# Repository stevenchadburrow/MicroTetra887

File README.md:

# MicroTetra887
<b>Two-player "Tetra" through 16-color VGA on a PIC16F887</b><br>

The goal of this project was a challenge to do more with less.  I have used the PIC24 and PIC32 various times to generate VGA signals and play video games, but the PIC16 has far less capability.  "Tetra" is very easy to implement and one of my favorite games, so it was the target for this device.  Space allowed for there to be two players simultaneously.

Specifications:<br>
- Only IC is the PIC16F887<br>
- Runs at 5 MIPS (20 MHz clock)<br>
- 368 bytes of RAM<br>
- VGA resolution of 24x22 pixels at 16 colors<br>
- Two-player "Tetra" through homebrew or Genesis controllers<br>
- PCB's double as both the console and controllers<br>

<table>
  <tr><td></td><td></td></tr>
  <tr><td></td><td></td></tr>
  <tr><td></td><td></td></tr>
</table>

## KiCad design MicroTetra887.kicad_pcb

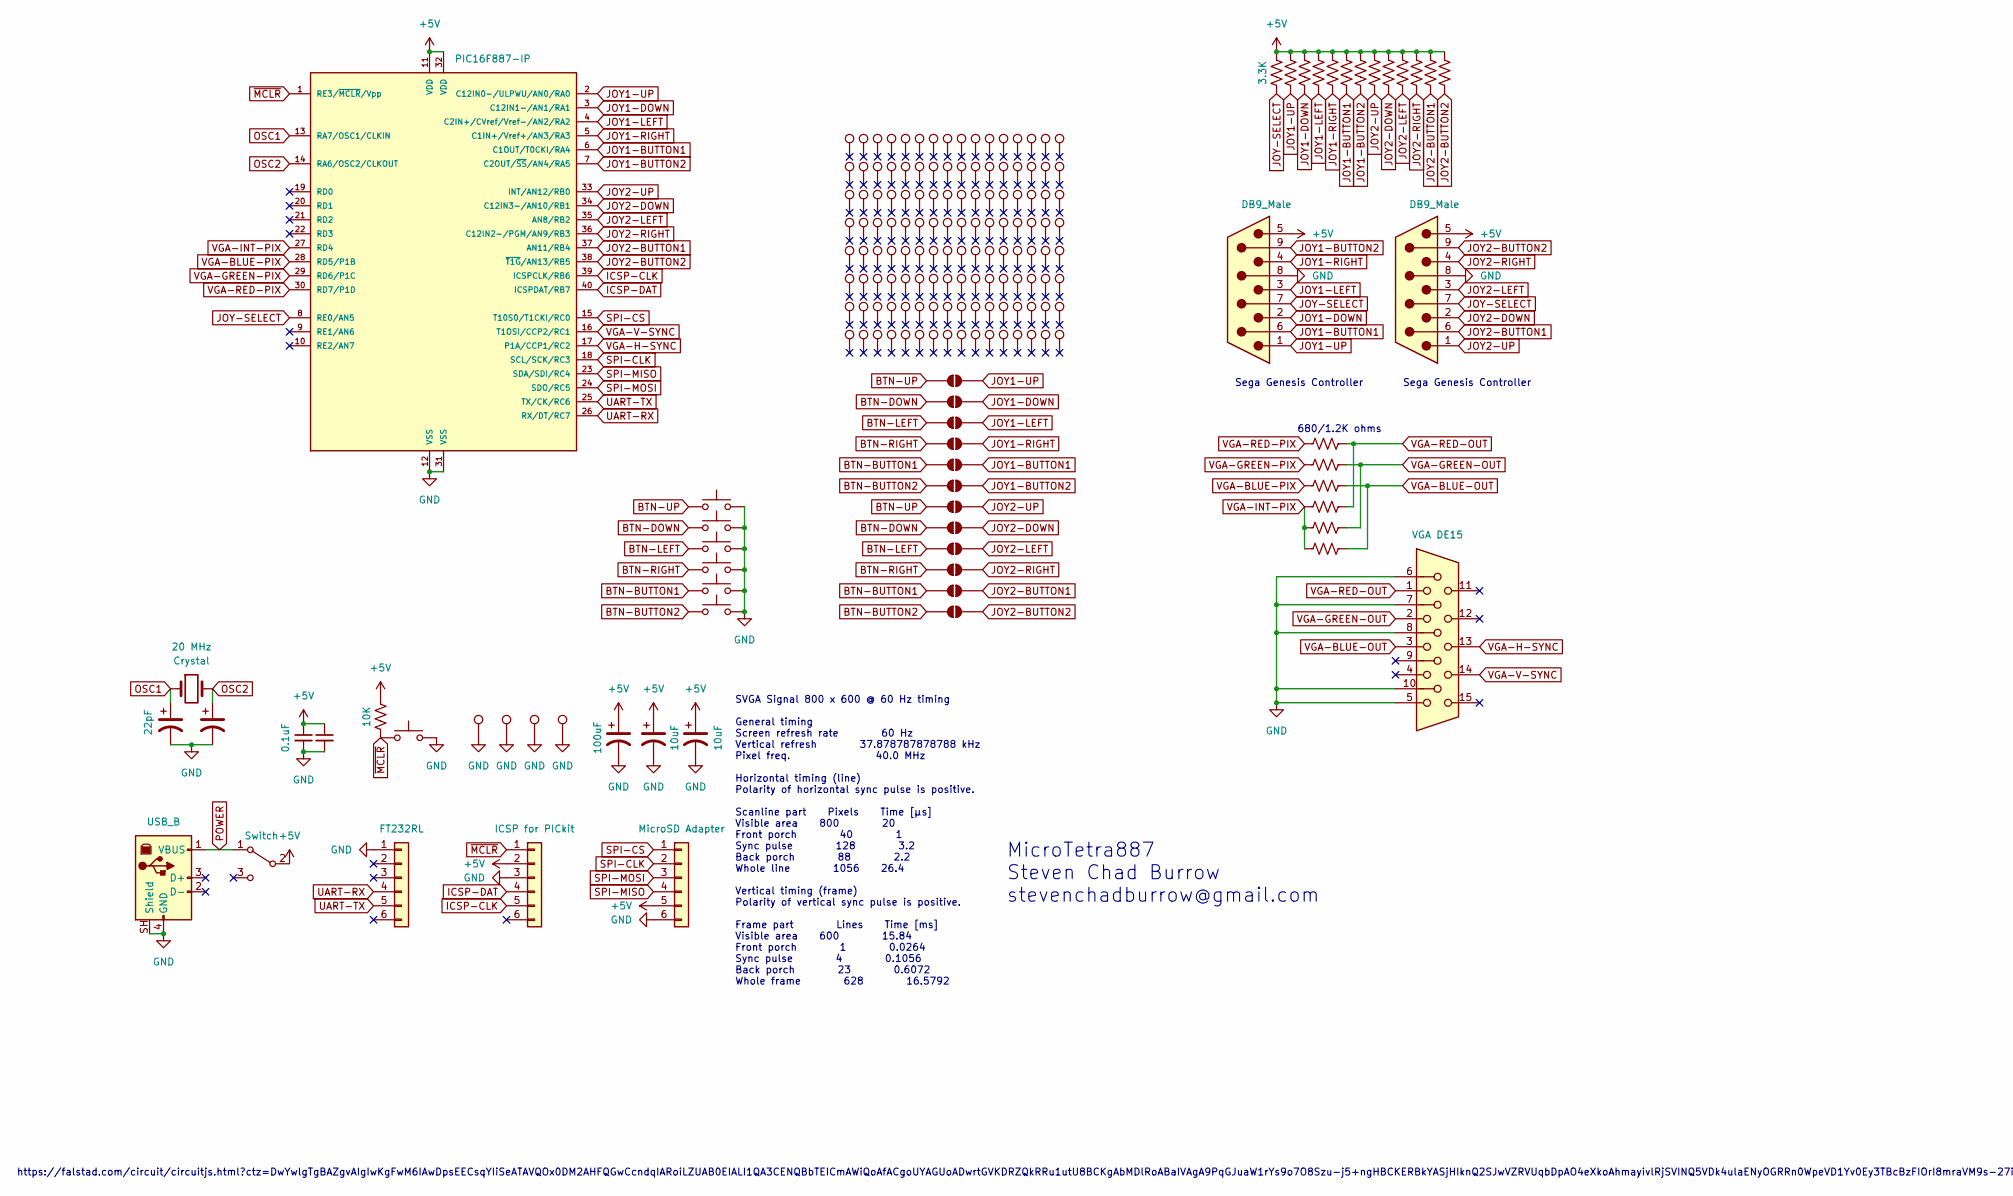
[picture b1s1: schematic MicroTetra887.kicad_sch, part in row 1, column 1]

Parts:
C1, C2: C_Polarized_US; CP_Radial_Tantal_D6.0mm_P2.50mm
C3, C4, C5: C_Polarized_US; CP_Radial_D8.0mm_P3.50mm
C8, C9: C_Small; C_Disc_D3.8mm_W2.6mm_P2.50mm
J1: USB_B; USB_B_Lumberg_2411_02_Horizontal
J8, J9: DB9_Male; DSUB-9_Pins_Horizontal_P2.77x2.84mm_EdgePinOffset7.70mm_Hou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
J11: VGA DE15; DSUB-15-HD_Socket_Horizontal_P2.29x2.54mm_EdgePinOffset8.35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
J14, J15, J16: Conn_01x06; PinSocket_1x06_P2.54mm_Horizontal
JP1, JP2, JP3, JP4, JP5, JP6, JP7, JP8, JP9, JP10, JP11, JP12: SolderJumper_2_Open; SolderJumper-2_P1.3mm_Open_Pad1.0x1.5mm
R9, R10, R11, R14, R15, R16, R17, R18, R19, R20, R21, R22, R23, R24, R25, R26, R27, R28, R29, R30: R_US; R_Axial_DIN0207_L6.3mm_D2.5mm_P10.16mm_Horizontal
SW1, SW2, SW3, SW4, SW5, SW6: SW_Push; SW_PUSH_6mm_H13mm
SW7: SW_SPDT; SW_E-Switch_EG1224_SPDT_Angled
SW11: SW_Push; SW_Tactile_SPST_Angled_PTS645Vx83-2LFS
TP1, TP2, TP3, TP4: TestPoint; ScrewHole-4-40
TP5, TP6, TP7, TP8, TP9, TP10, TP11, TP12, TP13, TP14, TP15, TP16, TP17, TP18, TP19, TP20, TP21, TP22, TP23, TP24, TP25, TP26, TP27, TP28, TP29, TP30, TP31, TP32, TP33, TP34, TP35, TP36, TP37, TP38, TP39, TP40, TP41, TP42, TP43, TP44, TP45, TP46, TP47, TP48, TP49, TP50, TP51, TP52, TP53, TP54, TP55, TP56, TP57, TP58, TP59, TP60, TP61, TP62, TP63, TP64, TP65, TP66, TP67, TP68, TP69, TP70, TP71, TP72, TP73, TP74, TP75, TP76, TP77, TP78, TP79, TP80, TP81, TP82, TP83, TP84, TP85, TP86, TP87, TP88, TP89, TP90, TP91, TP92, TP93, TP94, TP95, TP96, TP97, TP98, TP99, TP100, TP101, TP102, TP103, TP104, TP105, TP106, TP107, TP108, TP109, TP110, TP111, TP112, TP113, TP114, TP115, TP116, TP117, TP118, TP119, TP120, TP121, TP122, TP123, TP124, TP125, TP126, TP127, TP128, TP129, TP130, TP131, TP132: TestPoint; PinHeader_1x01_P2.54mm_Vertical_TestPoint
U1: PIC16F887-IP; DIP-40_W15.24mm_Socket
Y1: Crystal; Crystal_HC18-U_Vertical

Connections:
+5V: C3.1, C4.1, C5.1, C8.1, C9.1, J8.5, J9.5, J14.2, J16.5, R11.1, R18.1, R19.1, R20.1, R21.1, R22.1, R23.1, R24.1, R25.1, R26.1, R27.1, R28.1, R29.1, R30.1, SW7.2 (B), U1.11 (VDD), U1.32 (VDD)
BTN-BUTTON1: JP5.1 (A), JP11.1 (A), SW5.1
BTN-BUTTON2: JP6.1 (A), JP12.1 (A), SW6.1
BTN-DOWN: JP2.1 (A), JP8.1 (A), SW2.1
BTN-LEFT: JP3.1 (A), JP9.1 (A), SW3.1
BTN-RIGHT: JP4.1 (A), JP10.1 (A), SW4.1
BTN-UP: JP1.1 (A), JP7.1 (A), SW1.1
GND: C1.2, C2.2, C3.2, C4.2, C5.2, C8.2, C9.2, J1.4 (GND), J1.SH (Shield), J8.8, J9.8, J11.5, J11.6, J11.7, J11.8, J11.10, J14.3, J15.1, J16.6, SW1.2, SW2.2, SW3.2, SW4.2, SW5.2, SW6.2, SW11.2, TP1.1 (1_1), TP2.1 (1_1), TP3.1 (1_1), TP4.1 (1_1), U1.12 (VSS), U1.31 (VSS)
ICSP-CLK: J14.5, U1.39 (ICSPCLK/RB6)
ICSP-DAT: J14.4, U1.40 (ICSPDAT/RB7)
JOY1-BUTTON1: J8.6, JP5.2 (B), R23.2, U1.6 (C1OUT/T0CKI/RA4)
JOY1-BUTTON2: J8.9, JP6.2 (B), R24.2, U1.7 (C2OUT/~SS/AN4/RA5)
JOY1-DOWN: J8.2, JP2.2 (B), R20.2, U1.3 (C12IN1-/AN1/RA1)
JOY1-LEFT: J8.3, JP3.2 (B), R21.2, U1.4 (C2IN+/CVref/Vref-/AN2/RA2)
JOY1-RIGHT: J8.4, JP4.2 (B), R22.2, U1.5 (C1IN+/Vref+/AN3/RA3)
JOY1-UP: J8.1, JP1.2 (B), R19.2, U1.2 (C12IN0-/ULPWU/AN0/RA0)
JOY2-BUTTON1: J9.6, JP11.2 (B), R29.2, U1.37 (AN11/RB4)
JOY2-BUTTON2: J9.9, JP12.2 (B), R30.2, U1.38 (~T1G/AN13/RB5)
JOY2-DOWN: J9.2, JP8.2 (B), R26.2, U1.34 (C12IN3-/AN10/RB1)
JOY2-LEFT: J9.3, JP9.2 (B), R27.2, U1.35 (AN8/RB2)
JOY2-RIGHT: J9.4, JP10.2 (B), R28.2, U1.36 (C12IN2-/PGM/AN9/RB3)
JOY2-UP: J9.1, JP7.2 (B), R25.2, U1.33 (INT/AN12/RB0)
JOY-SELECT: J8.7, J9.7, R18.2, U1.8 (RE0/AN5)
OSC1: C1.1, U1.13 (RA7/OSC1/CLKIN), Y1.1
OSC2: C2.1, U1.14 (RA6/OSC2/CLKOUT), Y1.2
POWER: J1.1 (VBUS), SW7.1 (A)
SPI-CLK: J16.2, U1.18 (SCL/SCK/RC3)
SPI-CS: J16.1, U1.15 (T10S0/T1CKI/RC0)
SPI-MISO: J16.4, U1.23 (SDA/SDI/RC4)
SPI-MOSI: J16.3, U1.24 (SDO/RC5)
UART-RX: J15.4, U1.26 (RX/DT/RC7)
UART-TX: J15.5, U1.25 (TX/CK/RC6)
VGA-BLUE-OUT: J11.3, R16.1, R17.1
VGA-BLUE-PIX: R16.2, U1.28 (RD5/P1B)
VGA-GREEN-OUT: J11.2, R14.1, R15.1
VGA-GREEN-PIX: R14.2, U1.29 (RD6/P1C)
VGA-H-SYNC: J11.13, U1.17 (P1A/CCP1/RC2)
VGA-INT-PIX: R10.2, R15.2, R17.2, U1.27 (RD4)
VGA-RED-OUT: J11.1, R9.1, R10.1
VGA-RED-PIX: R9.2, U1.30 (RD7/P1D)
VGA-V-SYNC: J11.14, U1.16 (T1OSI/CCP2/RC1)
~MCLR: J14.1, R11.2, SW11.1, U1.1 (RE3/~MCLR/Vpp)

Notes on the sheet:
MicroTetra887 Steven Chad Burrow stevenchadburrow@gmail.com
Sega Genesis Controller
https://falstad.com/circuit/circuitjs.html?ctz=DwYwlgTgBAZgvAIgIwKgFwM6IAwDpsEECsqYIiSeATAVQOx0DM2AHFQGwCcndqIARoiLZUAB0EIALI1QA3CENQBbTEICmAWiQoAfACgoUYAGUoADwrtGVKDRZQkRRu1utU8BCKgAbMDlRoABaIVAgA9PqGJuaW1rYs9o7O8Szu-j5+ngHBCKERBkYASjHIknQ2SJwVZRVUqbDpAO4eXkoAhmayivlRjSVINQ5VDk4ulaENyOGRRn0WpeVD1Y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
680/1.2K ohms
SVGA Signal 800 x 600 @ 60 Hz timing General timing Screen refresh rate 60 Hz Vertical refresh 37.878787878788 kHz Pixel freq. 40.0 MHz Horizontal timing (line) Polarity of horizontal sync pulse is positive. Scanline part Pixels Time [µs] Visible area 800 20 Front porch 40 1 Sync pulse 128 3.2 Back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

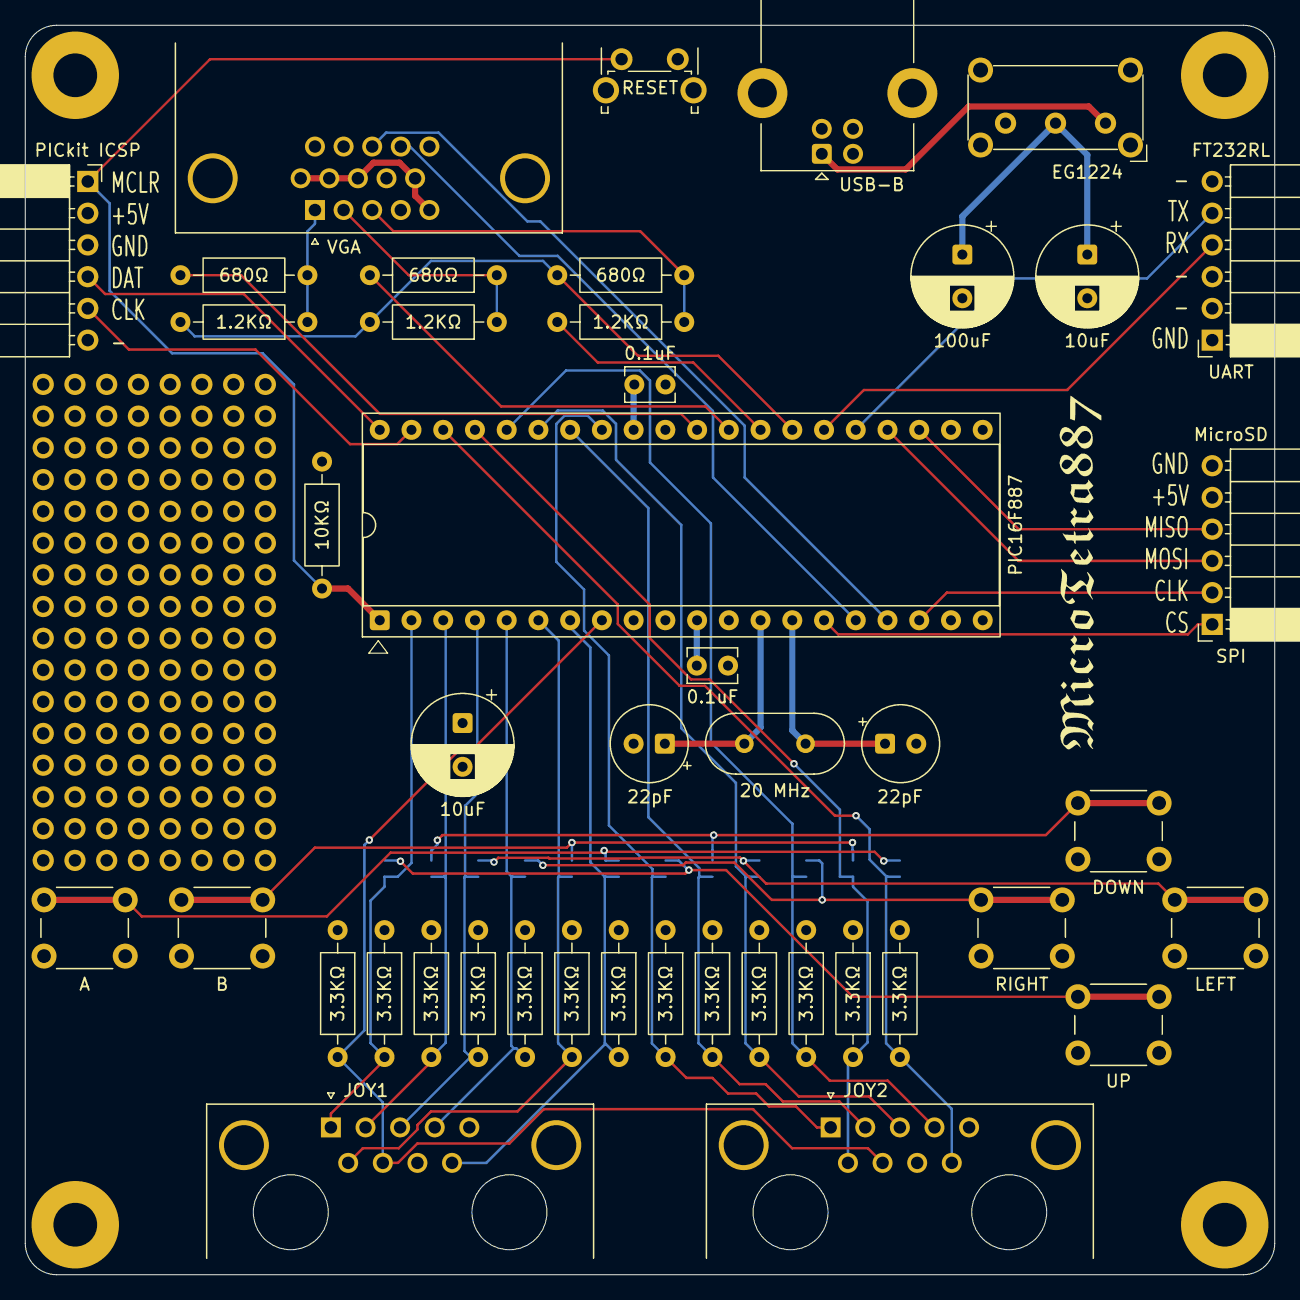
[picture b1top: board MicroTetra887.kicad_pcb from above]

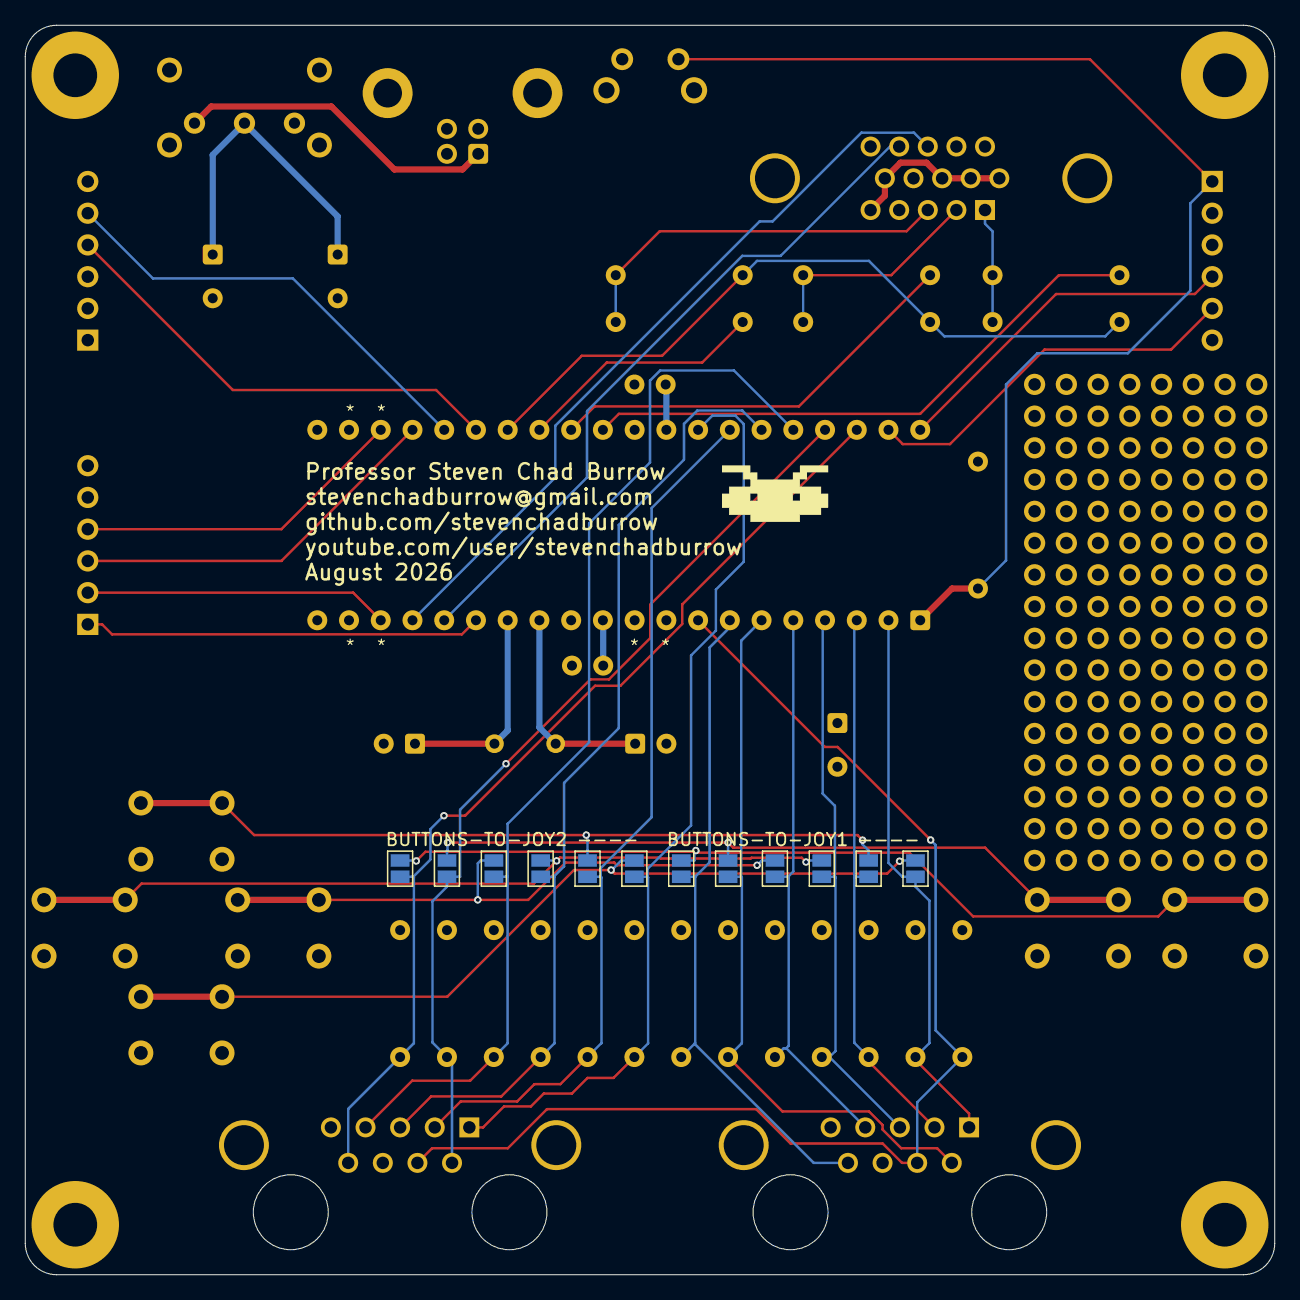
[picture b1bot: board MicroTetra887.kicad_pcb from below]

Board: 4 copper layers, 100.0 x 100.0 mm, 190 parts (13 on the bottom side), 42 nets.

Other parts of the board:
G100: LOGO; Logo
G101: LOGO; Title

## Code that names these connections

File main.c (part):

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// 'C' source line config statements

// CONFIG1
//#pragma config FOSC = INTRC_NOCLKOUT// Oscillator Selection bits (INTOSCIO oscillator: I/O function on RA6/OSC2/CLKOUT pin, I/O function on RA7/OSC1/CLKIN)
#pragma config FOSC = HS        // Oscillator Selection bits (HS oscillator: High-speed crystal/resonator on RA6/OSC2/CLKOUT and RA7/OSC1/CLKIN)
#pragma config WDTE = OFF       // Watchdog Timer Enable bit (WDT disabled and can be enabled by SWDTEN bit of the WDTCON register)
#pragma config PWRTE = OFF      // Power-up Timer Enable bit (PWRT disabled)
#pragma config MCLRE = ON       // RE3/MCLR pin function select bit (RE3/MCLR pin function is MCLR)
#pragma config CP = OFF         // Code Protection bit (Program memory code protection is disabled)
#pragma config CPD = OFF        // Data Code Protection bit (Data memory code protection is disabled)
#pragma config BOREN = OFF      // Brown Out Reset Selection bits (BOR disabled)
#pragma config IESO = ON        // Internal External Switchover bit (Internal/External Switchover mode is enabled)
#pragma config FCMEN = OFF      // Fail-Safe Clock Monitor Enabled bit (Fail-Safe Clock Monitor is disabled)
#pragma config LVP = OFF        // Low Voltage Programming Enable bit (RB3 pin has digital I/O, HV on MCLR must be used for programming)

// CONFIG2
#pragma config BOR4V = BOR40V   // Brown-out Reset Selection bit (Brown-out Reset set to 4.0V)
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
		if (vsync == 0 || vsync == 3) // sync pulse
		{
			PORTCbits.RC1 = 1; // V-SYNC positive

			// set TMR1 interrupt
			T1CON = 0x10; // prescaler = 1:2, disable timer
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
			// disable PWM signal and ground H-SYNC
			CCP1CON = 0x00; // disable PWM
			PORTCbits.RC2 = 0; // ground H-SYNC signal

			// nop padding
			asm("NOP");
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			asm("NOP");

			// set H-SYNC high
			PORTCbits.RC2 = 1;

			// nop padding
			asm("NOP");
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		}
		else if (vsync == 1) // back porch
		{
			PORTCbits.RC1 = 0; // V-SYNC negative
	
			// set TMR1 interrupt
			T1CON = 0x10; // prescaler = 1:2, disable timer
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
